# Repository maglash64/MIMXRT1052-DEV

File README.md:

# MIMXRT1052-DEV
MIMXRT1052 DEV BOARD (32MB RAM, 16MB FLASH, 40 pin RGB FFC, USB-C)
Under progress.

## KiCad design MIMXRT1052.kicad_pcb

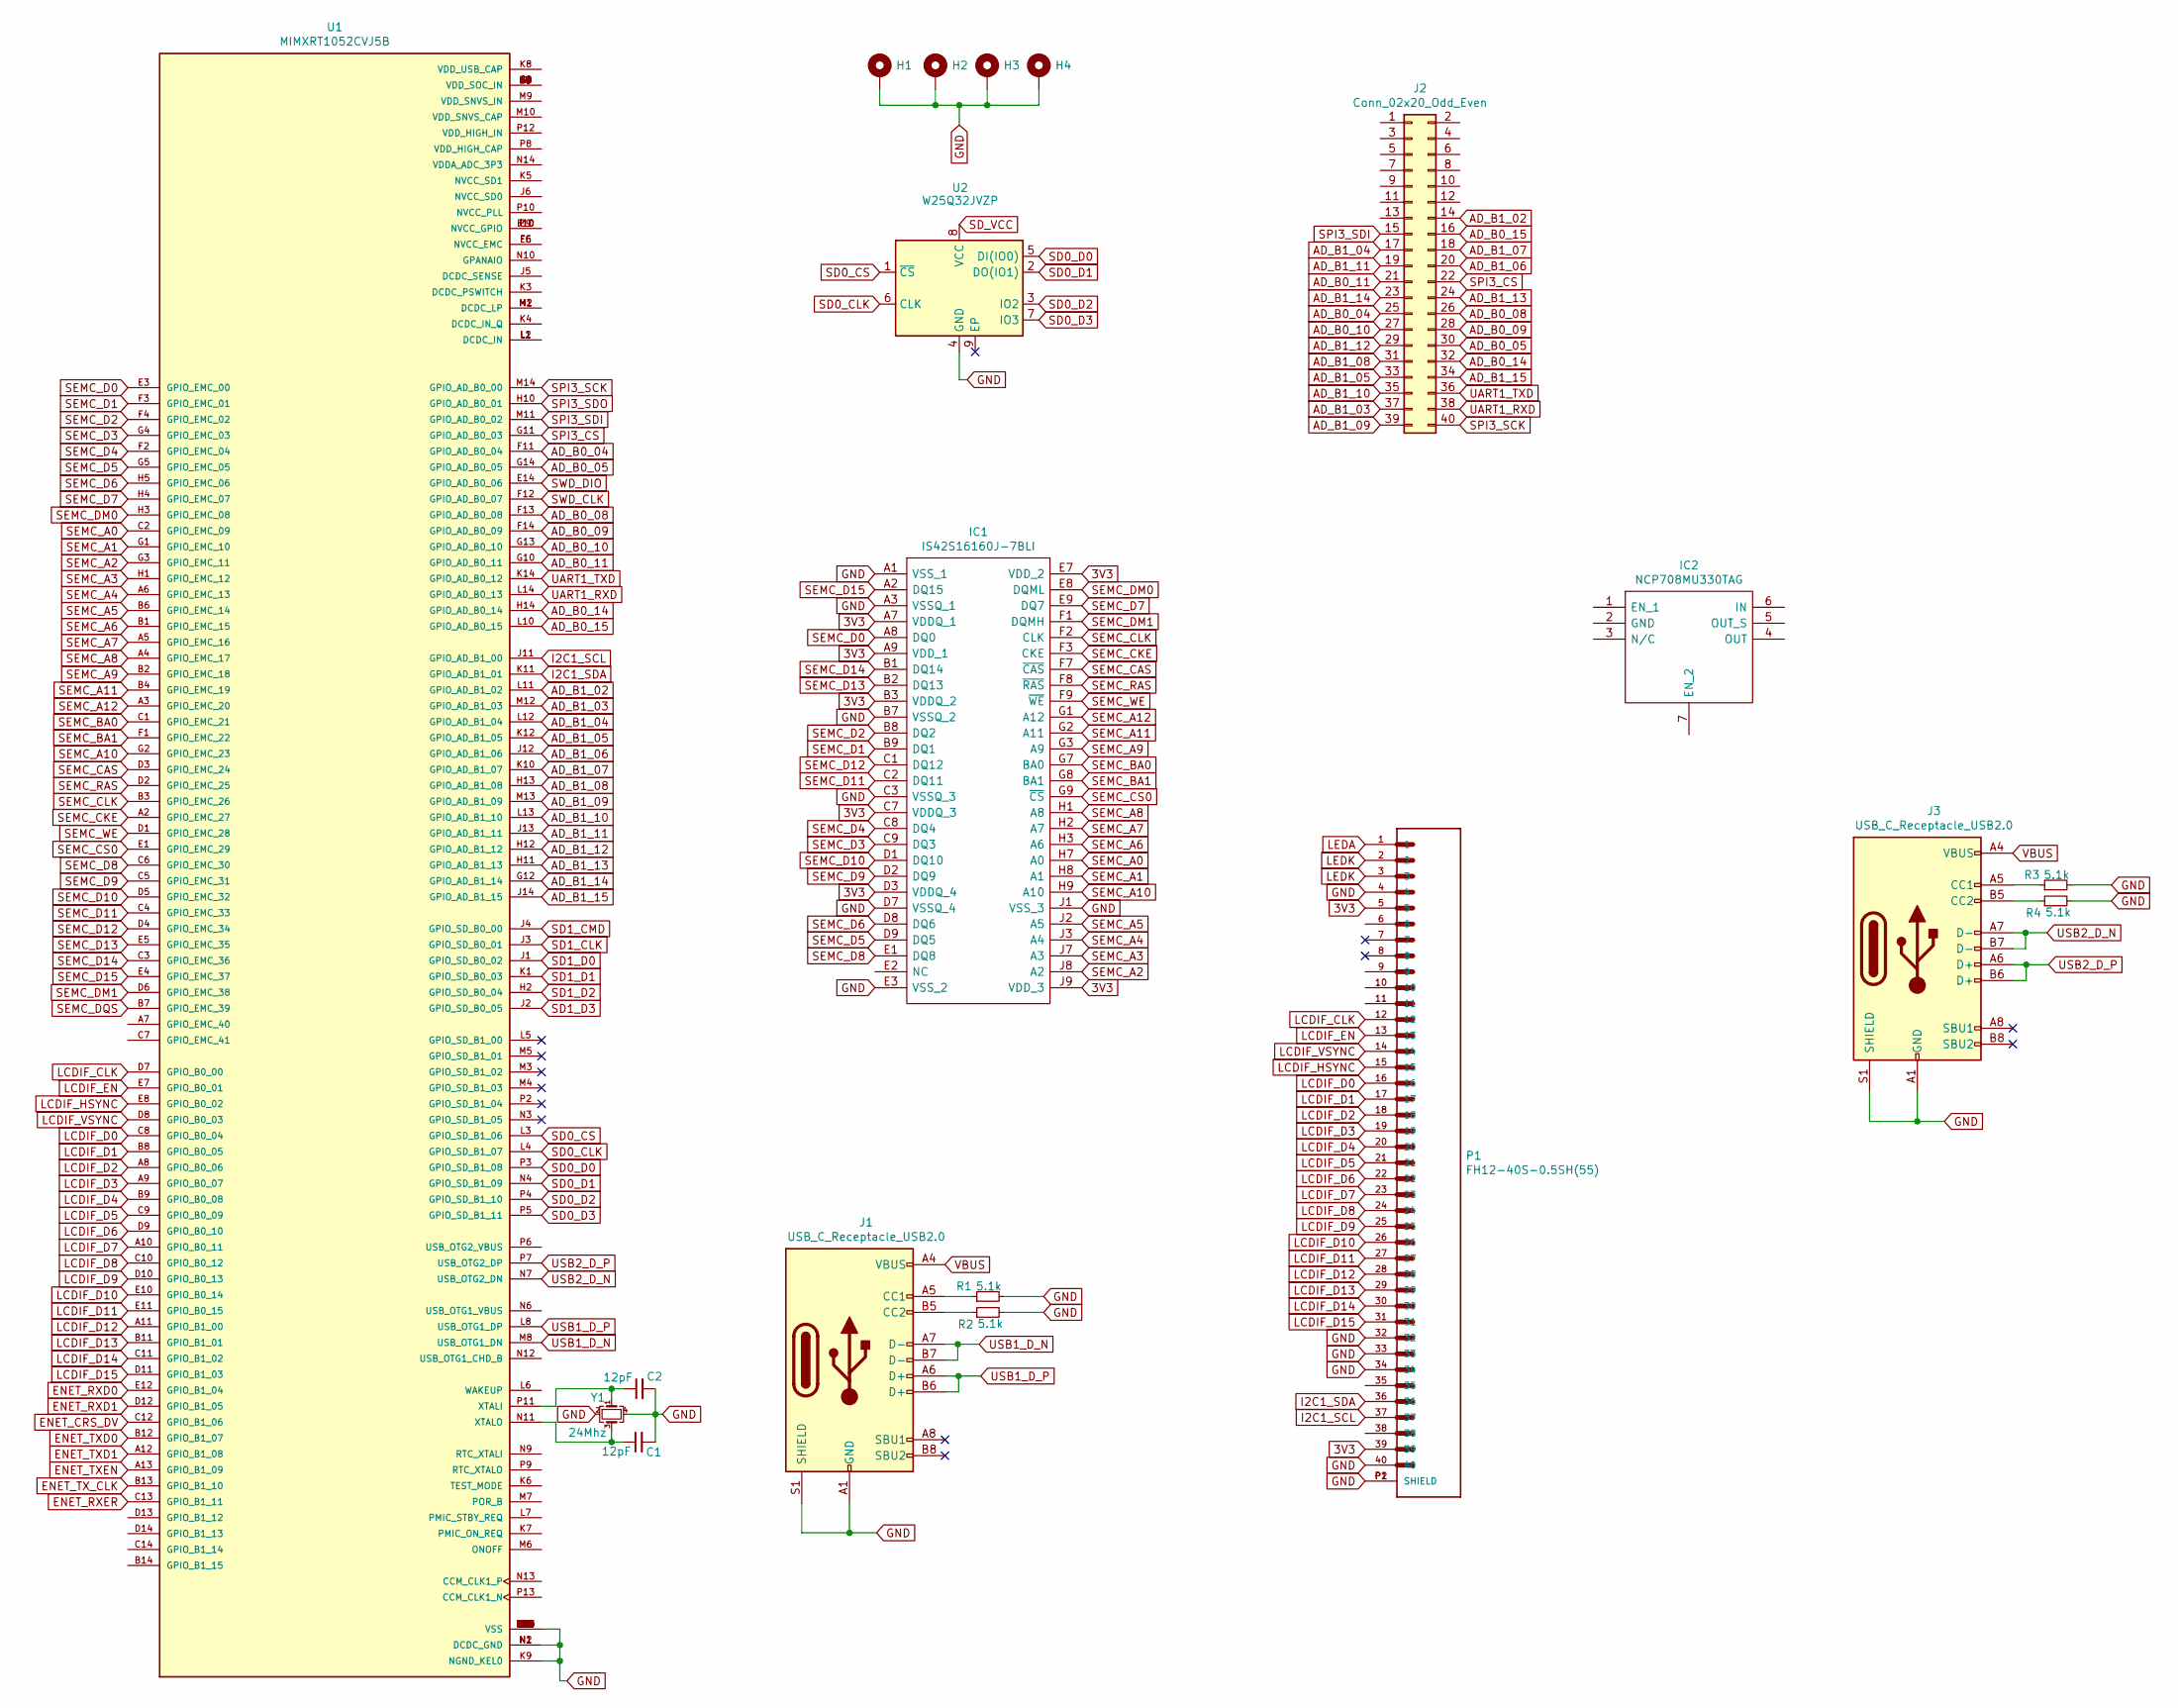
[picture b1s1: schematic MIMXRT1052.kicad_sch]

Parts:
C1, C2: 12pF; C_01005_0402Metric
H1, H2, H3, H4: MountingHole_Pad; MountingHole_2.7mm_M2.5_Pad_Via
IC1: IS42S16160J-7BLI; TFBGA-54; Mouser Part Number 870-42S16160J7BLI
IC2: NCP708MU330TAG; SON95P300X300X55-7N; Mouser Part Number 863-NCP708MU330TAG
J1, J3: USB_C_Receptacle_USB2.0; USB_C_Receptacle_HRO_TYPE-C-31-M-12
J2: Conn_02x20_Odd_Even; PinHeader_2x20_P2.54mm_Vertical
P1: FH12-40S-0.5SH(55); HRS_FH12-40S-0.5SH(55)
R1, R2, R3, R4: 5.1k; R_01005_0402Metric
U1: MIMXRT1052CVJ5B; BGA196C80P14X14_1200X1200X161N; PARTREV 1.2
U2: W25Q32JVZP; W25Q128JVEIQ
Y1: 24Mhz; Crystal_SMD_2520-4Pin_2.5x2.0mm

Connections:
3V3: IC1.A7 (VDDQ_1), IC1.A9 (VDD_1), IC1.B3 (VDDQ_2), IC1.C7 (VDDQ_3), IC1.D3 (VDDQ_4), IC1.E7 (VDD_2), IC1.J9 (VDD_3), P1.5, P1.39
AD_B0_04: J2.25, U1.F11 (GPIO_AD_B0_04)
AD_B0_05: J2.30, U1.G14 (GPIO_AD_B0_05)
AD_B0_08: J2.26, U1.F13 (GPIO_AD_B0_08)
AD_B0_09: J2.28, U1.F14 (GPIO_AD_B0_09)
AD_B0_10: J2.27, U1.G13 (GPIO_AD_B0_10)
AD_B0_11: J2.21, U1.G10 (GPIO_AD_B0_11)
AD_B0_14: J2.32, U1.H14 (GPIO_AD_B0_14)
AD_B0_15: J2.16, U1.L10 (GPIO_AD_B0_15)
AD_B1_02: J2.14, U1.L11 (GPIO_AD_B1_02)
AD_B1_03: J2.37, U1.M12 (GPIO_AD_B1_03)
AD_B1_04: J2.17, U1.L12 (GPIO_AD_B1_04)
AD_B1_05: J2.33, U1.K12 (GPIO_AD_B1_05)
AD_B1_06: J2.20, U1.J12 (GPIO_AD_B1_06)
AD_B1_07: J2.18, U1.K10 (GPIO_AD_B1_07)
AD_B1_08: J2.31, U1.H13 (GPIO_AD_B1_08)
AD_B1_09: J2.39, U1.M13 (GPIO_AD_B1_09)
AD_B1_10: J2.35, U1.L13 (GPIO_AD_B1_10)
AD_B1_11: J2.19, U1.J13 (GPIO_AD_B1_11)
AD_B1_12: J2.29, U1.H12 (GPIO_AD_B1_12)
AD_B1_13: J2.24, U1.H11 (GPIO_AD_B1_13)
AD_B1_14: J2.23, U1.G12 (GPIO_AD_B1_14)
AD_B1_15: J2.34, U1.J14 (GPIO_AD_B1_15)
ENET_CRS_DV: U1.C12 (GPIO_B1_06)
ENET_RXD0: U1.E12 (GPIO_B1_04)
ENET_RXD1: U1.D12 (GPIO_B1_05)
ENET_RXER: U1.C13 (GPIO_B1_11)
ENET_TXD0: U1.B12 (GPIO_B1_07)
ENET_TXD1: U1.A12 (GPIO_B1_08)
ENET_TXEN: U1.A13 (GPIO_B1_09)
ENET_TX_CLK: U1.B13 (GPIO_B1_10)
GND: C1.2, C2.2, H1.1, H2.1, H3.1, H4.1, IC1.A1 (VSS_1), IC1.A3 (VSSQ_1), IC1.B7 (VSSQ_2), IC1.C3 (VSSQ_3), IC1.D7 (VSSQ_4), IC1.E3 (VSS_2), IC1.J1 (VSS_3), J1.A1 (GND), J1.A12 (GND), J1.B1 (GND), J1.B12 (GND), J1.S1 (SHIELD), J3.A1 (GND), J3.A12 (GND), J3.B1 (GND), J3.B12 (GND), J3.S1 (SHIELD), P1.4, P1.32, P1.33, P1.34, P1.40, P1.P1 (SHIELD), P1.P2 (SHIELD), R1.2, R2.2, R3.2, R4.2, U1.A1 (VSS), U1.A14 (VSS), U1.B5 (VSS), U1.B10 (VSS), U1.E2 (VSS), U1.E13 (VSS), U1.G7 (VSS), U1.G8 (VSS), U1.H7 (VSS), U1.H8 (VSS), U1.J7 (VSS), U1.J8 (VSS), U1.K2 (VSS), U1.K9 (NGND_KEL0), U1.K13 (VSS), U1.L9 (VSS), U1.N1 (DCDC_GND), U1.N2 (DCDC_GND), U1.N5 (VSS), U1.N8 (VSS), U1.P1 (VSS), U1.P14 (VSS), U2.4 (GND), Y1.2, Y1.4
I2C1_SCL: P1.37, U1.J11 (GPIO_AD_B1_00)
I2C1_SDA: P1.36, U1.K11 (GPIO_AD_B1_01)
LCDIF_CLK: P1.12, U1.D7 (GPIO_B0_00)
LCDIF_D0: P1.16, U1.C8 (GPIO_B0_04)
LCDIF_D1: P1.17, U1.B8 (GPIO_B0_05)
LCDIF_D2: P1.18, U1.A8 (GPIO_B0_06)
LCDIF_D3: P1.19, U1.A9 (GPIO_B0_07)
LCDIF_D4: P1.20, U1.B9 (GPIO_B0_08)
LCDIF_D5: P1.21, U1.C9 (GPIO_B0_09)
LCDIF_D6: P1.22, U1.D9 (GPIO_B0_10)
LCDIF_D7: P1.23, U1.A10 (GPIO_B0_11)
LCDIF_D8: P1.24, U1.C10 (GPIO_B0_12)
LCDIF_D9: P1.25, U1.D10 (GPIO_B0_13)
LCDIF_D10: P1.26, U1.E10 (GPIO_B0_14)
LCDIF_D11: P1.27, U1.E11 (GPIO_B0_15)
LCDIF_D12: P1.28, U1.A11 (GPIO_B1_00)
LCDIF_D13: P1.29, U1.B11 (GPIO_B1_01)
LCDIF_D14: P1.30, U1.C11 (GPIO_B1_02)
LCDIF_D15: P1.31, U1.D11 (GPIO_B1_03)
LCDIF_EN: P1.13, U1.E7 (GPIO_B0_01)
LCDIF_HSYNC: P1.15, U1.E8 (GPIO_B0_02)
LCDIF_VSYNC: P1.14, U1.D8 (GPIO_B0_03)
LEDA: P1.1
LEDK: P1.2, P1.3
unnamed: C1.1, U1.N11 (XTALO), Y1.3
unnamed: C2.1, U1.P11 (XTALI), Y1.1
unnamed: J1.A5 (CC1), R1.1
unnamed: J1.B5 (CC2), R2.1
unnamed: J3.A5 (CC1), R3.1
unnamed: J3.B5 (CC2), R4.1
unnamed: U1.E6 (NVCC_EMC), U1.F5 (NVCC_EMC)
unnamed: U1.E9 (NVCC_GPIO), U1.F10 (NVCC_GPIO), U1.J10 (NVCC_GPIO)
unnamed: U1.F6 (VDD_SOC_IN), U1.F7 (VDD_SOC_IN), U1.F8 (VDD_SOC_IN), U1.F9 (VDD_SOC_IN), U1.G6 (VDD_SOC_IN), U1.G9 (VDD_SOC_IN), U1.H6 (VDD_SOC_IN), U1.H9 (VDD_SOC_IN), U1.J9 (VDD_SOC_IN)
unnamed: U1.L1 (DCDC_IN), U1.L2 (DCDC_IN)
unnamed: U1.M1 (DCDC_LP), U1.M2 (DCDC_LP)
SD0_CLK: U1.L4 (GPIO_SD_B1_07), U2.6 (CLK)
SD0_CS: U1.L3 (GPIO_SD_B1_06), U2.1 (~CS)
SD0_D0: U1.P3 (GPIO_SD_B1_08), U2.5 (DI(IO0))
SD0_D1: U1.N4 (GPIO_SD_B1_09), U2.2 (DO(IO1))
SD0_D2: U1.P4 (GPIO_SD_B1_10), U2.3 (IO2)
SD0_D3: U1.P5 (GPIO_SD_B1_11), U2.7 (IO3)
SD1_CLK: U1.J3 (GPIO_SD_B0_01)
SD1_CMD: U1.J4 (GPIO_SD_B0_00)
SD1_D0: U1.J1 (GPIO_SD_B0_02)
SD1_D1: U1.K1 (GPIO_SD_B0_03)
SD1_D2: U1.H2 (GPIO_SD_B0_04)
SD1_D3: U1.J2 (GPIO_SD_B0_05)
SD_VCC: U2.8 (VCC)
SEMC_A0: IC1.H7 (A0), U1.C2 (GPIO_EMC_09)
SEMC_A1: IC1.H8 (A1), U1.G1 (GPIO_EMC_10)
SEMC_A2: IC1.J8 (A2), U1.G3 (GPIO_EMC_11)
SEMC_A3: IC1.J7 (A3), U1.H1 (GPIO_EMC_12)
SEMC_A4: IC1.J3 (A4), U1.A6 (GPIO_EMC_13)
SEMC_A5: IC1.J2 (A5), U1.B6 (GPIO_EMC_14)
SEMC_A6: IC1.H3 (A6), U1.B1 (GPIO_EMC_15)
SEMC_A7: IC1.H2 (A7), U1.A5 (GPIO_EMC_16)
SEMC_A8: IC1.H1 (A8), U1.A4 (GPIO_EMC_17)
SEMC_A9: IC1.G3 (A9), U1.B2 (GPIO_EMC_18)
SEMC_A10: IC1.H9 (A10), U1.G2 (GPIO_EMC_23)
SEMC_A11: IC1.G2 (A11), U1.B4 (GPIO_EMC_19)
SEMC_A12: IC1.G1 (A12), U1.A3 (GPIO_EMC_20)
SEMC_BA0: IC1.G7 (BA0), U1.C1 (GPIO_EMC_21)
SEMC_BA1: IC1.G8 (BA1), U1.F1 (GPIO_EMC_22)
SEMC_CAS: IC1.F7 (~CAS), U1.D3 (GPIO_EMC_24)
SEMC_CKE: IC1.F3 (CKE), U1.A2 (GPIO_EMC_27)
SEMC_CLK: IC1.F2 (CLK), U1.B3 (GPIO_EMC_26)
SEMC_CS0: IC1.G9 (~CS), U1.E1 (GPIO_EMC_29)
SEMC_D0: IC1.A8 (DQ0), U1.E3 (GPIO_EMC_00)
SEMC_D1: IC1.B9 (DQ1), U1.F3 (GPIO_EMC_01)
SEMC_D2: IC1.B8 (DQ2), U1.F4 (GPIO_EMC_02)
SEMC_D3: IC1.C9 (DQ3), U1.G4 (GPIO_EMC_03)
SEMC_D4: IC1.C8 (DQ4), U1.F2 (GPIO_EMC_04)
SEMC_D5: IC1.D9 (DQ5), U1.G5 (GPIO_EMC_05)
SEMC_D6: IC1.D8 (DQ6), U1.H5 (GPIO_EMC_06)
SEMC_D7: IC1.E9 (DQ7), U1.H4 (GPIO_EMC_07)
SEMC_D8: IC1.E1 (DQ8), U1.C6 (GPIO_EMC_30)
SEMC_D9: IC1.D2 (DQ9), U1.C5 (GPIO_EMC_31)
SEMC_D10: IC1.D1 (DQ10), U1.D5 (GPIO_EMC_32)
SEMC_D11: IC1.C2 (DQ11), U1.C4 (GPIO_EMC_33)
SEMC_D12: IC1.C1 (DQ12), U1.D4 (GPIO_EMC_34)
SEMC_D13: IC1.B2 (DQ13), U1.E5 (GPIO_EMC_35)
SEMC_D14: IC1.B1 (DQ14), U1.C3 (GPIO_EMC_36)
SEMC_D15: IC1.A2 (DQ15), U1.E4 (GPIO_EMC_37)
SEMC_DM0: IC1.E8 (DQML), U1.H3 (GPIO_EMC_08)
SEMC_DM1: IC1.F1 (DQMH), U1.D6 (GPIO_EMC_38)
SEMC_DQS: U1.B7 (GPIO_EMC_39)
SEMC_RAS: IC1.F8 (~RAS), U1.D2 (GPIO_EMC_25)
SEMC_WE: IC1.F9 (~WE), U1.D1 (GPIO_EMC_28)
SPI3_CS: J2.22, U1.G11 (GPIO_AD_B0_03)
SPI3_SCK: J2.40, U1.M14 (GPIO_AD_B0_00)
SPI3_SDI: J2.15, U1.M11 (GPIO_AD_B0_02)
SPI3_SDO: U1.H10 (GPIO_AD_B0_01)
SWD_CLK: U1.F12 (GPIO_AD_B0_07)
SWD_DIO: U1.E14 (GPIO_AD_B0_06)
UART1_RXD: J2.38, U1.L14 (GPIO_AD_B0_13)
UART1_TXD: J2.36, U1.K14 (GPIO_AD_B0_12)
USB1_D_N: J1.A7 (D-), J1.B7 (D-), U1.M8 (USB_OTG1_DN)
USB1_D_P: J1.A6 (D+), J1.B6 (D+), U1.L8 (USB_OTG1_DP)
USB2_D_N: J3.A7 (D-), J3.B7 (D-), U1.N7 (USB_OTG2_DN)
USB2_D_P: J3.A6 (D+), J3.B6 (D+), U1.P7 (USB_OTG2_DP)
VBUS: J1.A4 (VBUS), J1.A9 (VBUS), J1.B4 (VBUS), J1.B9 (VBUS), J3.A4 (VBUS), J3.A9 (VBUS), J3.B4 (VBUS), J3.B9 (VBUS)

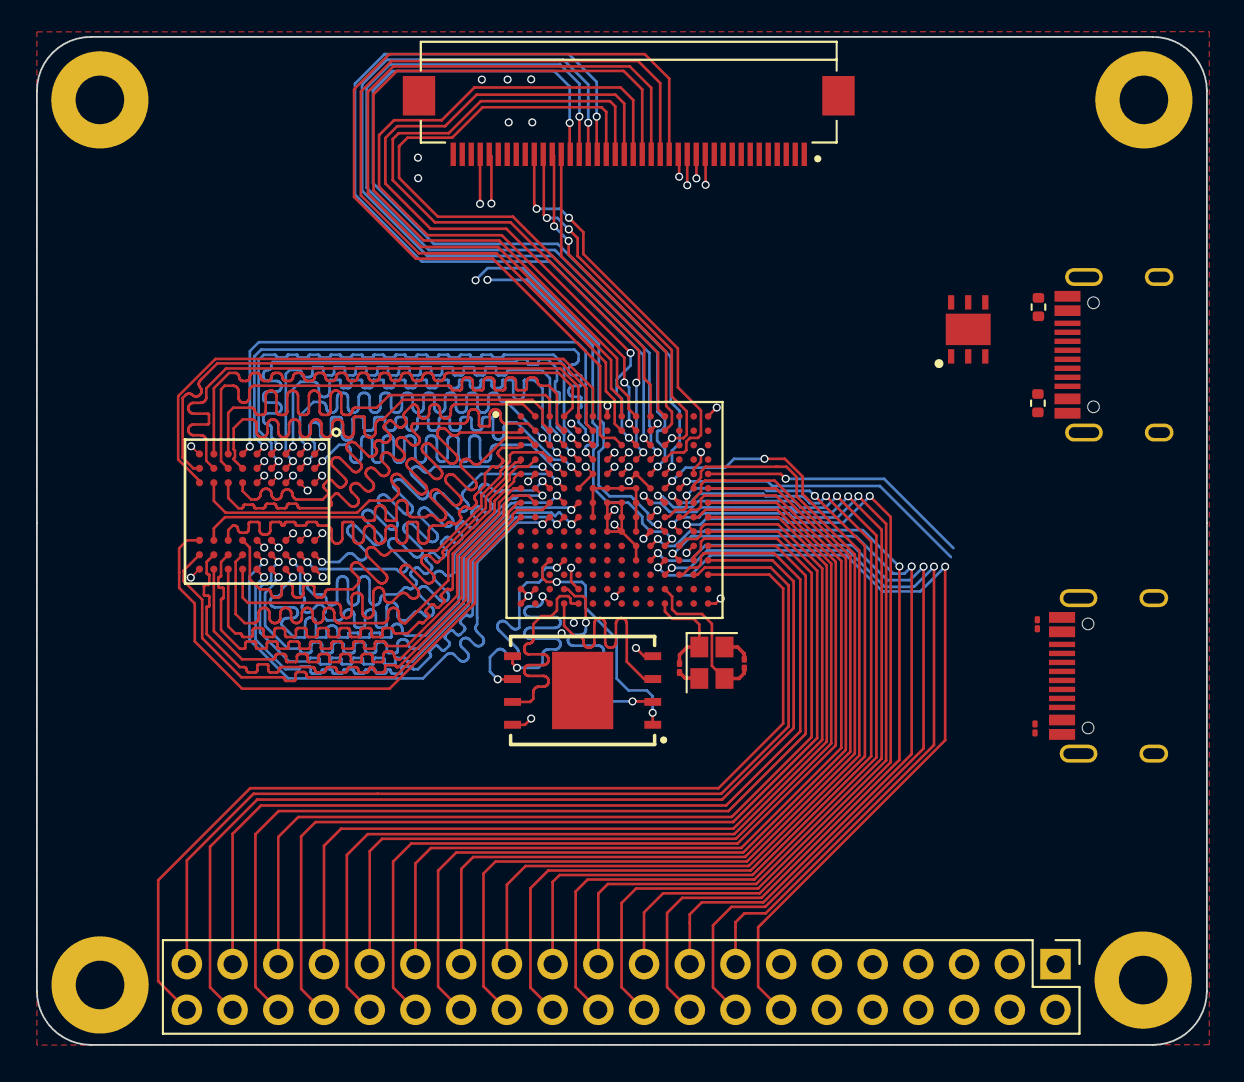
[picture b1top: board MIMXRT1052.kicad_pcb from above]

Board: 4 copper layers, 65.0 x 56.0 mm, 19 parts (0 on the bottom side), 113 nets.

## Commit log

2020-12-07 uploaded.
2020-12-07 updated.
